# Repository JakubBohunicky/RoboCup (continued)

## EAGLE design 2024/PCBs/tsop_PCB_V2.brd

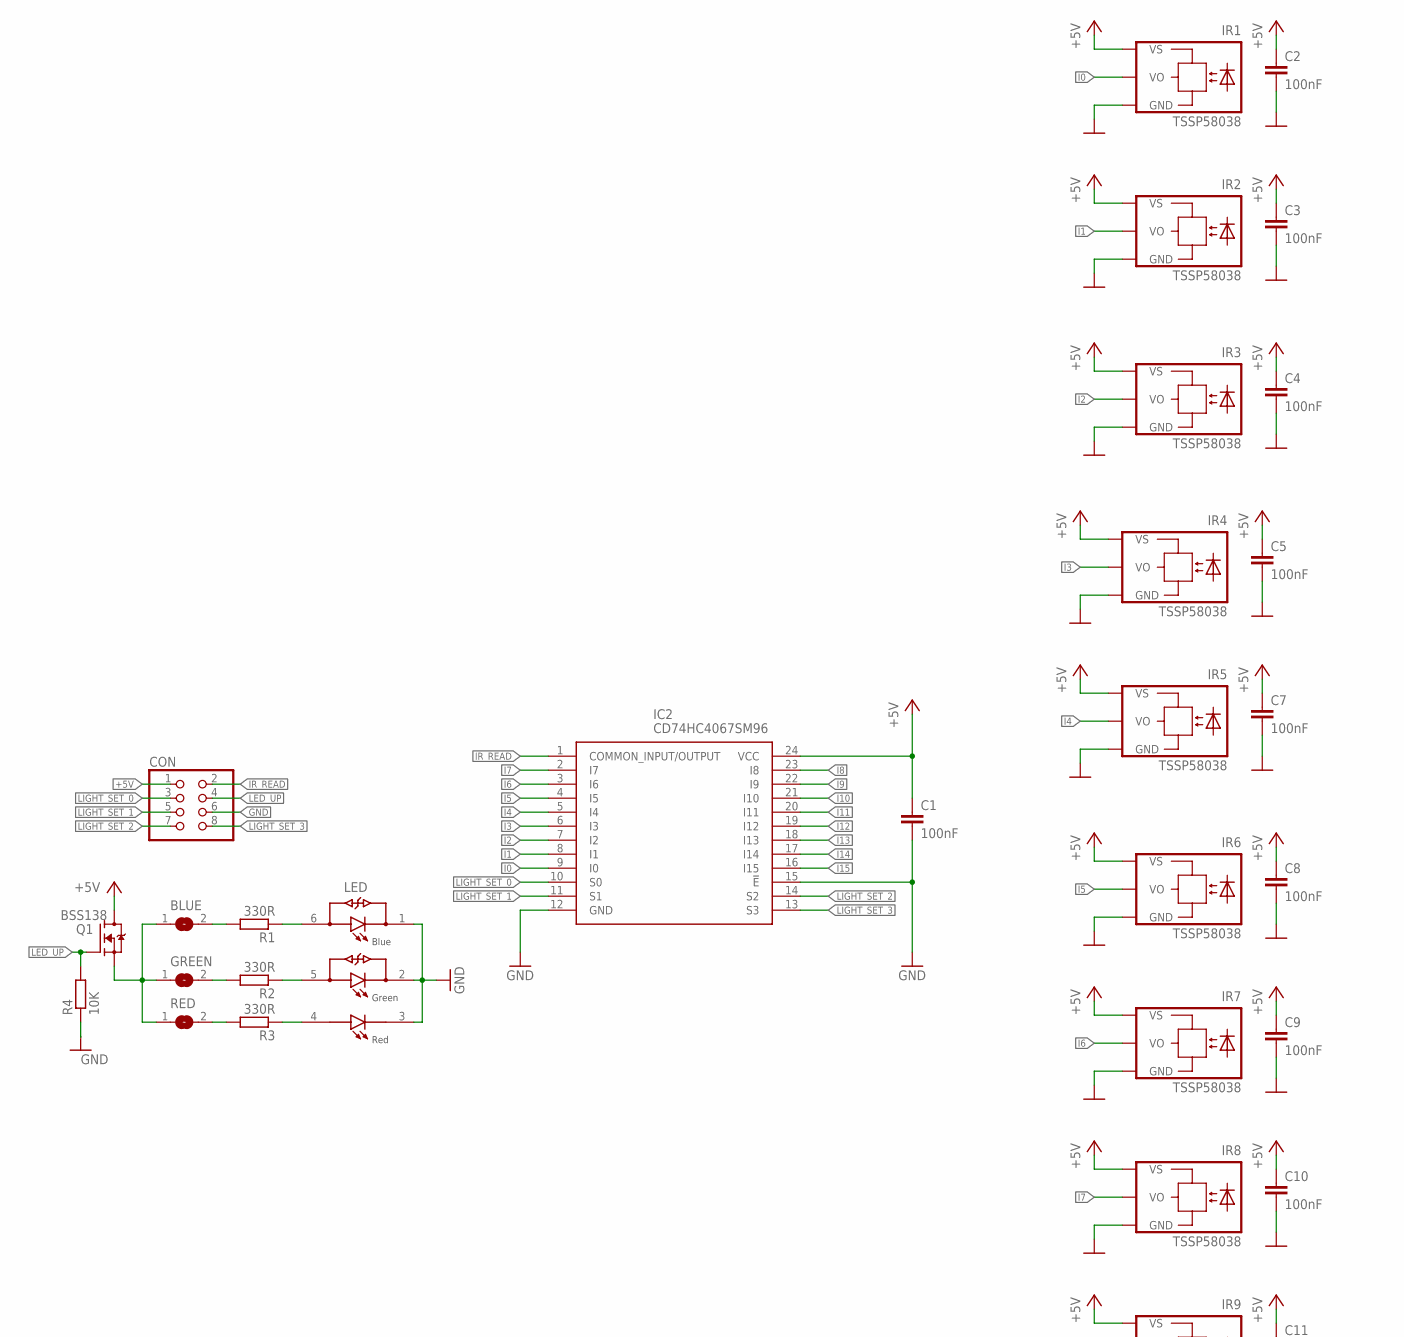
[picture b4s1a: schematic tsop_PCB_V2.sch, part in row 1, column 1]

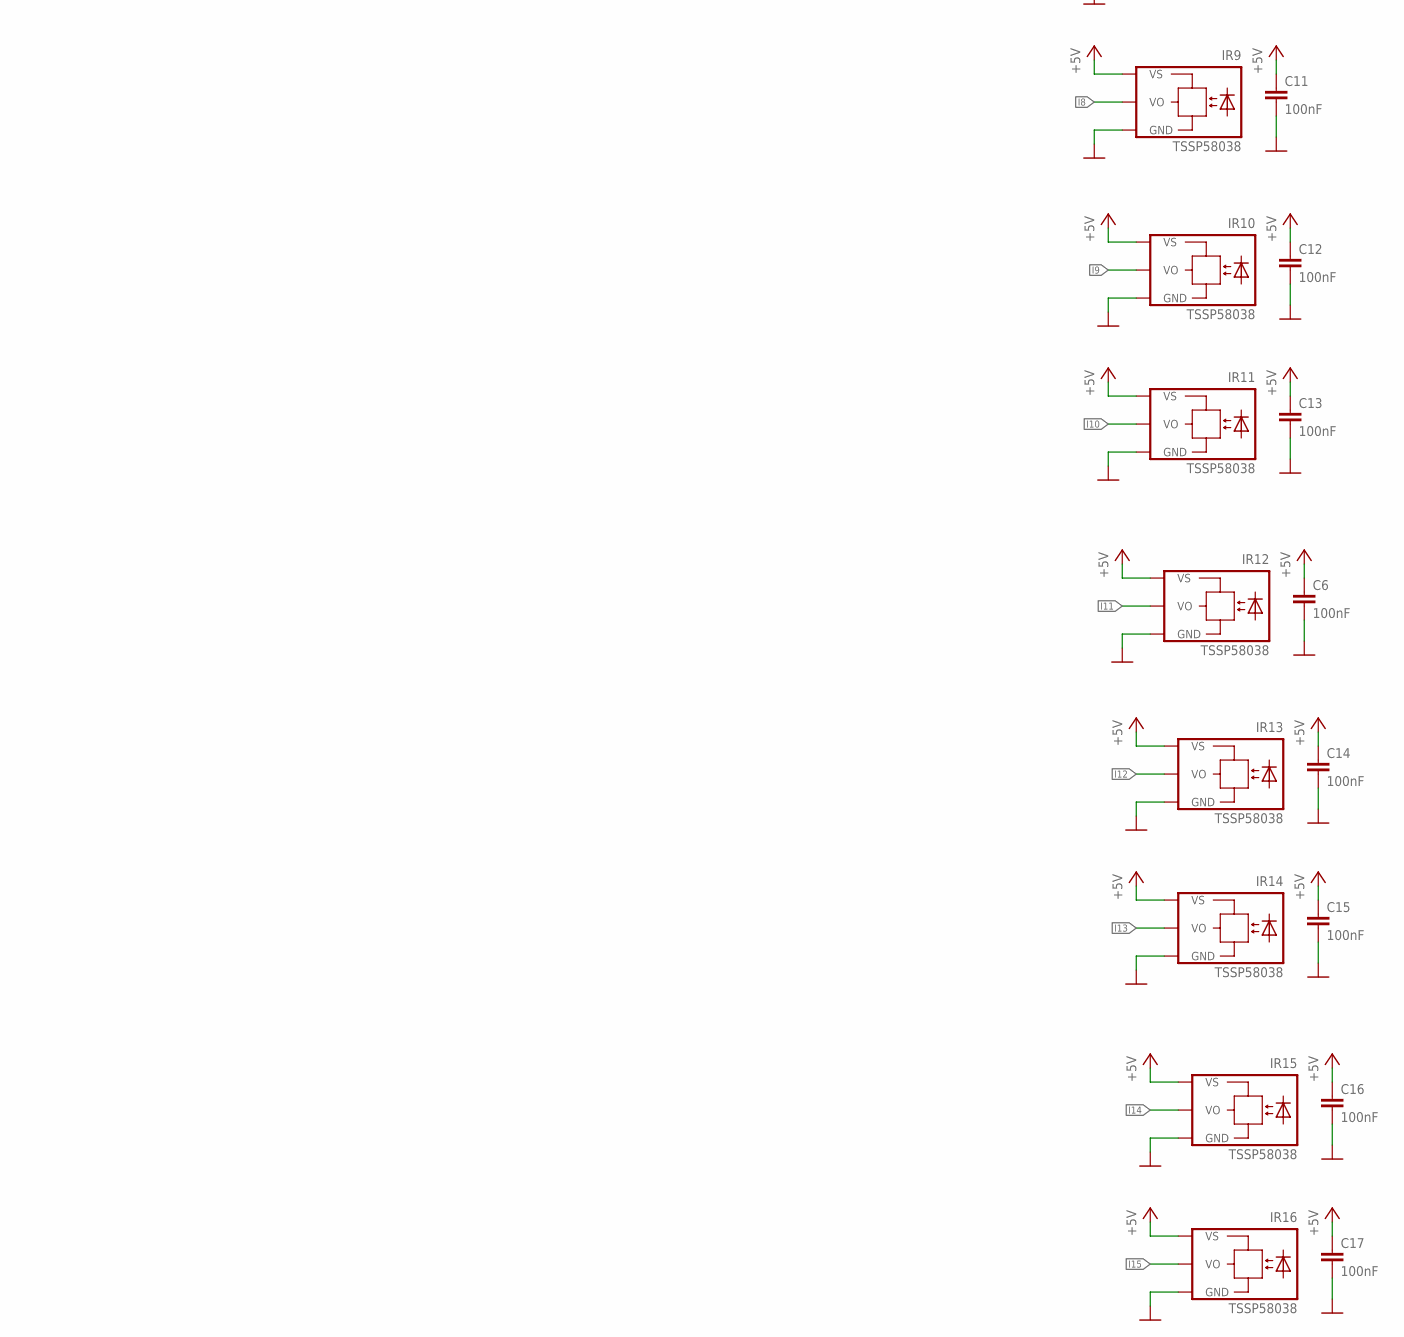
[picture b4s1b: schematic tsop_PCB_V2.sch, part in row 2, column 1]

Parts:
BLUE: SJ
C1, C2, C3, C4, C5, C6, C7, C8, C9, C10, C11, C12, C13, C14, C15, C16, C17: 100nF; C0805
CON: PINHD-2X4; 2X04
GREEN: SJ
IC2: CD74HC4067SM96; SOP65P780X200-24N
IR1, IR2, IR3, IR4, IR5, IR6, IR7, IR8, IR9, IR10, IR11, IR12, IR13, IR14, IR15, IR16: TSSP58038; TSOP
LED: LTST-G563ZEGBW; LED_LTST-G563ZEGBW
Q1: BSS138; SOT95P240X111-3N
R1, R2, R3: 330R; R1206
R4: 10K; R1206
RED: SJ

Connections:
+5V: C1.1, C2.1, C3.1, C4.1, C5.1, C6.1, C7.1, C8.1, C9.1, C10.1, C11.1, C12.1, C13.1, C14.1, C15.1, C16.1, C17.1, CON.1, IC2.24 (VCC), IR1.VS, IR2.VS, IR3.VS, IR4.VS, IR5.VS, IR6.VS, IR7.VS, IR8.VS, IR9.VS, IR10.VS, IR11.VS, IR12.VS, IR13.VS, IR14.VS, IR15.VS, IR16.VS, Q1.3 (D)
GND: C1.2, C2.2, C3.2, C4.2, C5.2, C6.2, C7.2, C8.2, C9.2, C10.2, C11.2, C12.2, C13.2, C14.2, C15.2, C16.2, C17.2, CON.6, IC2.12 (GND), IC2.15 (!E), IR1.GND, IR2.GND, IR3.GND, IR4.GND, IR5.GND, IR6.GND, IR7.GND, IR8.GND, IR9.GND, IR10.GND, IR11.GND, IR12.GND, IR13.GND, IR14.GND, IR15.GND, IR16.GND, LED.1, LED.2, LED.3, R4.1
I0: IC2.9 (I0), IR1.VO
I1: IC2.8 (I1), IR2.VO
I2: IC2.7 (I2), IR3.VO
I3: IC2.6 (I3), IR4.VO
I4: IC2.5 (I4), IR5.VO
I5: IC2.4 (I5), IR6.VO
I6: IC2.3 (I6), IR7.VO
I7: IC2.2 (I7), IR8.VO
I8: IC2.23 (I8), IR9.VO
I9: IC2.22 (I9), IR10.VO
I10: IC2.21 (I10), IR11.VO
I11: IC2.20 (I11), IR12.VO
I12: IC2.19 (I12), IR13.VO
I13: IC2.18 (I13), IR14.VO
I14: IC2.17 (I14), IR15.VO
I15: IC2.16 (I15), IR16.VO
IR_READ: CON.2, IC2.1 (COMMON_INPUT/OUTPUT)
LED_UP: CON.4, Q1.1 (G), R4.2
LIGHT_SET_0: CON.3, IC2.10 (S0)
LIGHT_SET_1: CON.5, IC2.11 (S1)
LIGHT_SET_2: CON.7, IC2.14 (S2)
LIGHT_SET_3: CON.8, IC2.13 (S3)
unnamed: LED.6, R1.1
unnamed: LED.5, R2.1
unnamed: LED.4, R3.1
unnamed: R3.2, RED.2
unnamed: GREEN.2, R2.2
unnamed: BLUE.2, R1.2
unnamed: BLUE.1, GREEN.1, Q1.2 (S), RED.1

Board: 2 copper layers, 44 parts (0 on the bottom side), 31 nets, no tracks yet.

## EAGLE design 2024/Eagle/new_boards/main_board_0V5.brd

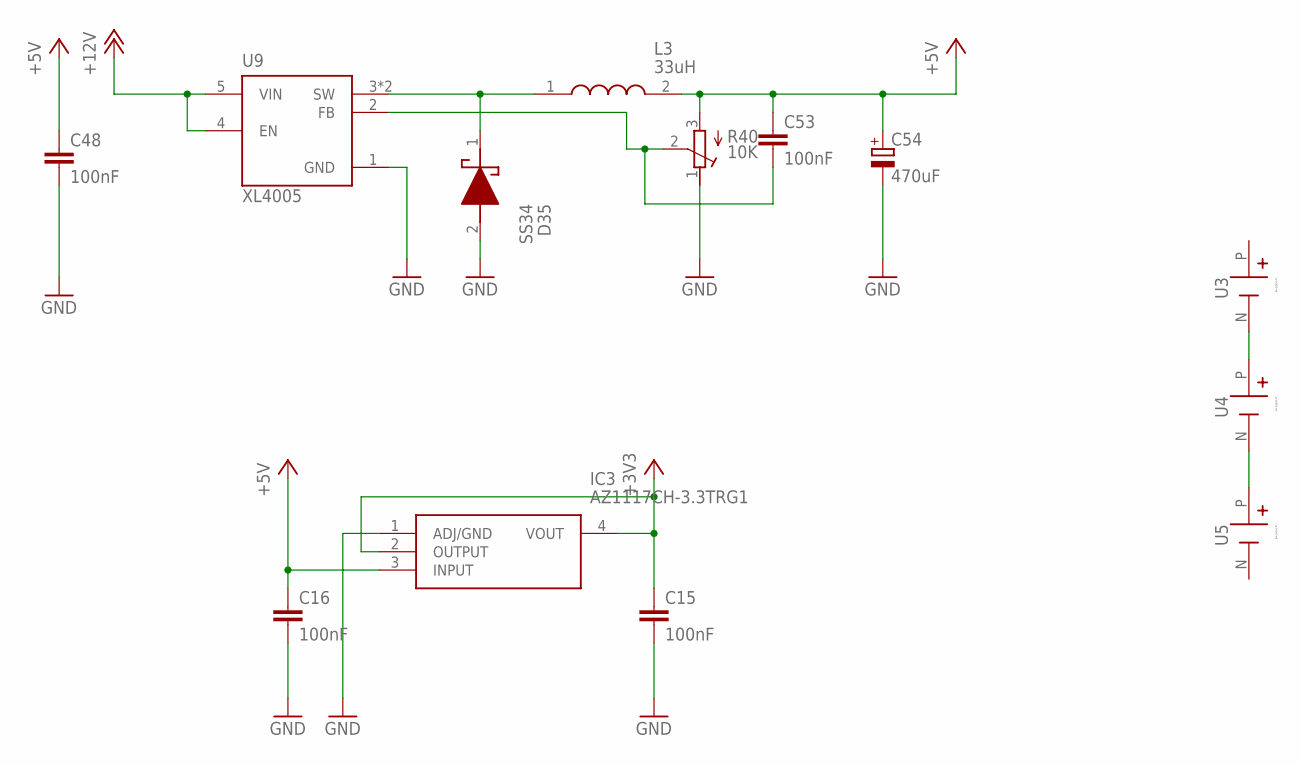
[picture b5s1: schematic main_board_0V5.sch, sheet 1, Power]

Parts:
C15, C16, C48, C53: 100nF; C0805
C54: 470uF; 150CLZ-1010
D35: SS34; DIOM8059X256N
IC3: AZ1117CH-3.3TRG1; SOT230P700X180-4N
L3: 33uH; WE-HCI_1350/136523
R40: 10K; RTRIM3314J
U3, U4, U5: BH-18650-PC; BAT_BH-18650-PC
U9: XL4005; CONV_XL4015

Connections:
+3V3: C15.1, IC3.2 (OUTPUT), IC3.4 (VOUT)
+5V: C16.1, C48.1, C53.1, C54.+, IC3.3 (INPUT), L3.2, R40.3 (A); also elsewhere on the board
+12V: U9.4 (EN), U9.5 (VIN); also elsewhere on the board
GND: C15.2, C16.2, C48.2, C54.-, D35.2 (A), IC3.1 (ADJ/GND), R40.1 (E), U9.1 (GND); also elsewhere on the board
unnamed: U4.N (-), U5.P (+)
unnamed: U3.N (-), U4.P (+)
unnamed: D35.1 (K), L3.1, U9.3 (SW), U9.3.1 (SW)
unnamed: C53.2, R40.2 (S), U9.2 (FB)

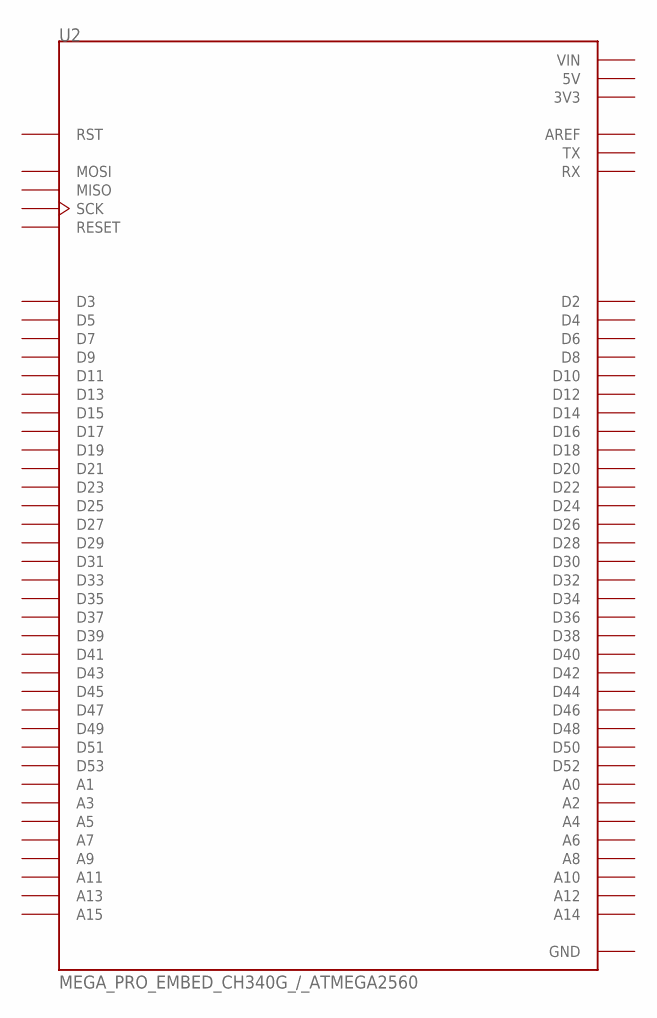
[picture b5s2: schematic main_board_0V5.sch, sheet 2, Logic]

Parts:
U2: MEGA_PRO_EMBED_CH340G_/_ATMEGA2560; MODULE_MEGA_PRO_EMBED_CH340G_/_ATMEGA2560

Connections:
3V3: U2.3V3_1 (3V3), U2.3V3_2 (3V3)
5V: U2.5V_1 (5V), U2.5V_2 (5V), U2.5V_3 (5V)
GND: U2.GND_1 (GND), U2.GND_2 (GND), U2.GND_3 (GND); also elsewhere on the board

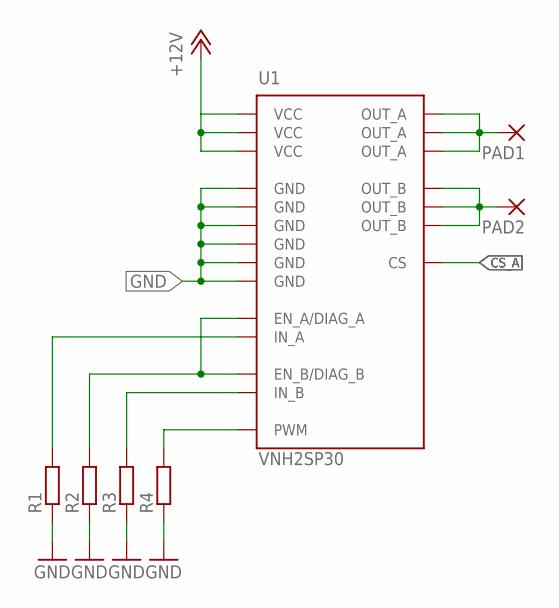
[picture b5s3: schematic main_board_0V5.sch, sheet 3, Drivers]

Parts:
PAD1, PAD2: 3,81/1,4
R1, R2, R3, R4: R-EU_R0805; R0805
U1: VNH2SP30; MULTIPOWER30

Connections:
+12V: U1.P$3 (VCC), U1.P$13 (VCC), U1.P$23 (VCC); also elsewhere on the board
CS_A: U1.P$9 (CS)
GND: R1.1, R2.1, R3.1, R4.1, U1.P$18 (GND), U1.P$19 (GND), U1.P$20 (GND), U1.P$26 (GND), U1.P$27 (GND), U1.P$28 (GND); also elsewhere on the board
unnamed: R4.2, U1.P$8 (PWM)
unnamed: R3.2, U1.P$11 (IN_B)
unnamed: R1.2, U1.P$5 (IN_A)
unnamed: R2.2, U1.P$6 (EN_A/DIAG_A), U1.P$10 (EN_B/DIAG_B)
unnamed: PAD2.1, U1.P$15 (OUT_B), U1.P$16 (OUT_B), U1.P$21 (OUT_B)
unnamed: PAD1.1, U1.P$1 (OUT_A), U1.P$25 (OUT_A), U1.P$30 (OUT_A)

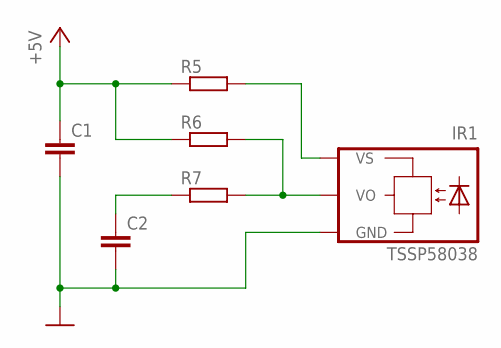
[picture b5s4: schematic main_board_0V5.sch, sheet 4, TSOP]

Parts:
C1, C2: C-EUC0805; C0805
IR1: TSSP58038; TSOP
R5, R6, R7: R-EU_R0805; R0805

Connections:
+5V: C1.1, R5.1, R6.1; also elsewhere on the board
GND: C1.2, C2.2, IR1.GND; also elsewhere on the board
unnamed: IR1.VS, R5.2
unnamed: C2.1, R7.1
unnamed: IR1.VO, R6.2, R7.2

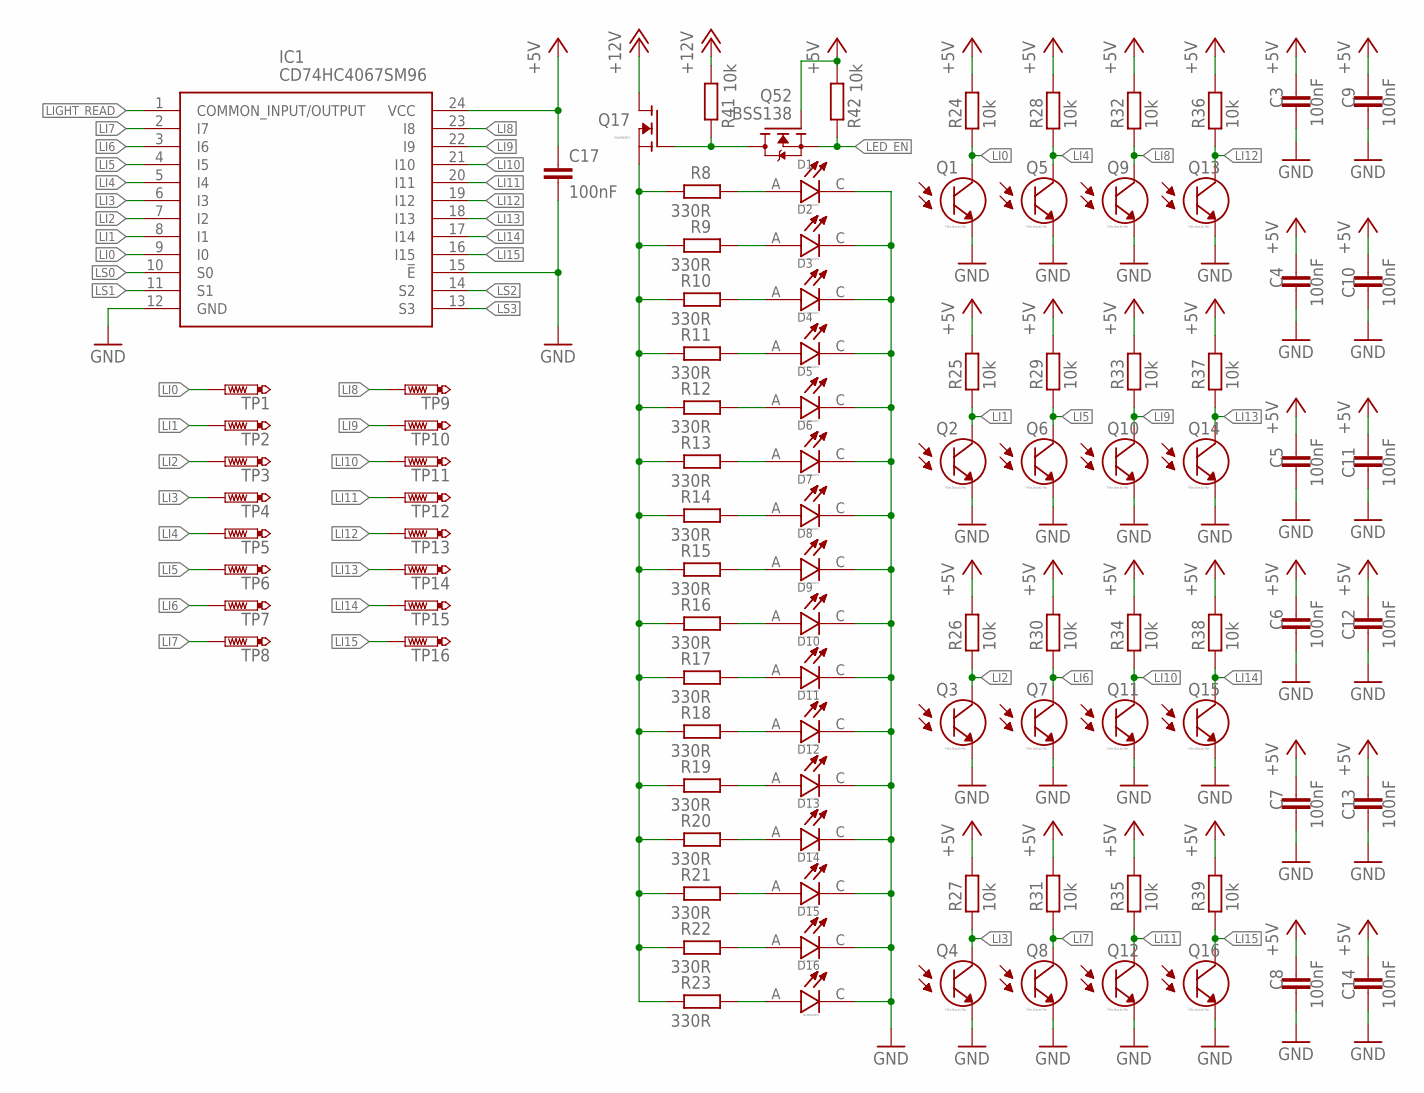
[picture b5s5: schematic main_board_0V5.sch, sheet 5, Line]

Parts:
C3, C4, C5, C6, C7, C8, C9, C10, C11, C12, C13, C14, C17: 100nF; C0805
D1, D2, D3, D4, D5, D6, D7, D8, D9, D10, D11, D12, D13, D14, D15, D16: OF-SMD2835Y; LED_OF-SMD2835Y
IC1: CD74HC4067SM96; SOP65P780X200-24N
Q1, Q2, Q3, Q4, Q5, Q6, Q7, Q8, Q9, Q10, Q11, Q12, Q13, Q14, Q15, Q16: PT19-21B/L41/TR8; XDCR_PT19-21B/L41/TR8
Q17: CSD19503KCS; TO254P1036X470X1965-3
Q52: BSS138; SOT95P240X111-3N
R8, R9, R10, R11, R12, R13, R14, R15, R16, R17, R18, R19, R20, R21, R22, R23: 330R; R0805
R24, R25, R26, R27, R28, R29, R30, R31, R32, R33, R34, R35, R36, R37, R38, R39: 10k; R0805
R41, R42: 10k; R1206
TP1, TP2, TP3, TP4, TP5, TP6, TP7, TP8, TP9, TP10, TP11, TP12, TP13, TP14, TP15, TP16: PTR1PAD1-13; P1-13

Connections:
+5V: C3.2, C4.2, C5.2, C6.2, C7.2, C8.2, C9.2, C10.2, C11.2, C12.2, C13.2, C14.2, C17.1, IC1.24 (VCC), Q52.1 (G), R24.1, R25.1, R26.1, R27.1, R28.1, R29.1, R30.1, R31.1, R32.1, R33.1, R34.1, R35.1, R36.1, R37.1, R38.1, R39.1, R42.2; also elsewhere on the board
+5V_UP: R41.2
+12V: Q17.2 (D); also elsewhere on the board
GND: C3.1, C4.1, C5.1, C6.1, C7.1, C8.1, C9.1, C10.1, C11.1, C12.1, C13.1, C14.1, C17.2, IC1.12 (GND), IC1.15 (!E), Q1.E, Q2.E, Q3.E, Q4.E, Q5.E, Q6.E, Q7.E, Q8.E, Q9.E, Q10.E, Q11.E, Q12.E, Q13.E, Q14.E, Q15.E, Q16.E; also elsewhere on the board
LED_EN: Q52.2 (S), R42.1
LI0: IC1.9 (I0), Q1.C, R24.2, TP1.TP
LI1: IC1.8 (I1), Q2.C, R25.2, TP2.TP
LI2: IC1.7 (I2), Q3.C, R26.2, TP3.TP
LI3: IC1.6 (I3), Q4.C, R27.2, TP4.TP
LI4: IC1.5 (I4), Q5.C, R28.2, TP5.TP
LI5: IC1.4 (I5), Q6.C, R29.2, TP6.TP
LI6: IC1.3 (I6), Q7.C, R30.2, TP7.TP
LI7: IC1.2 (I7), Q8.C, R31.2, TP8.TP
LI8: IC1.23 (I8), Q9.C, R32.2, TP9.TP
LI9: IC1.22 (I9), Q10.C, R33.2, TP10.TP
LI10: IC1.21 (I10), Q11.C, R34.2, TP11.TP
LI11: IC1.20 (I11), Q12.C, R35.2, TP12.TP
LI12: IC1.19 (I12), Q13.C, R36.2, TP13.TP
LI13: IC1.18 (I13), Q14.C, R37.2, TP14.TP
LI14: IC1.17 (I14), Q15.C, R38.2, TP15.TP
LI15: IC1.16 (I15), Q16.C, R39.2, TP16.TP
LIGHT_READ: IC1.1 (COMMON_INPUT/OUTPUT)
LS0: IC1.10 (S0)
LS1: IC1.11 (S1)
LS2: IC1.14 (S2)
LS3: IC1.13 (S3)
unnamed: D1.A, R8.1
unnamed: D9.A, R16.1
unnamed: D10.A, R17.1
unnamed: D2.A, R9.1
unnamed: D11.A, R18.1
unnamed: D3.A, R10.1
unnamed: D12.A, R19.1
unnamed: D4.A, R11.1
unnamed: D13.A, R20.1
unnamed: D5.A, R12.1
unnamed: D14.A, R21.1
unnamed: D6.A, R13.1
unnamed: D15.A, R22.1
unnamed: D7.A, R14.1
unnamed: D16.A, R23.1
unnamed: D8.A, R15.1
unnamed: D1.C, D2.C, D3.C, D4.C, D5.C, D6.C, D7.C, D8.C, D9.C, D10.C, D11.C, D12.C, D13.C, D14.C, D15.C, D16.C
unnamed: Q17.3 (S), R8.2, R9.2, R10.2, R11.2, R12.2, R13.2, R14.2, R15.2, R16.2, R17.2, R18.2, R19.2, R20.2, R21.2, R22.2, R23.2
unnamed: Q17.1 (G), Q52.3 (D), R41.1

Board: 2 copper layers, 125 parts (0 on the bottom side), 55 nets, no tracks yet.

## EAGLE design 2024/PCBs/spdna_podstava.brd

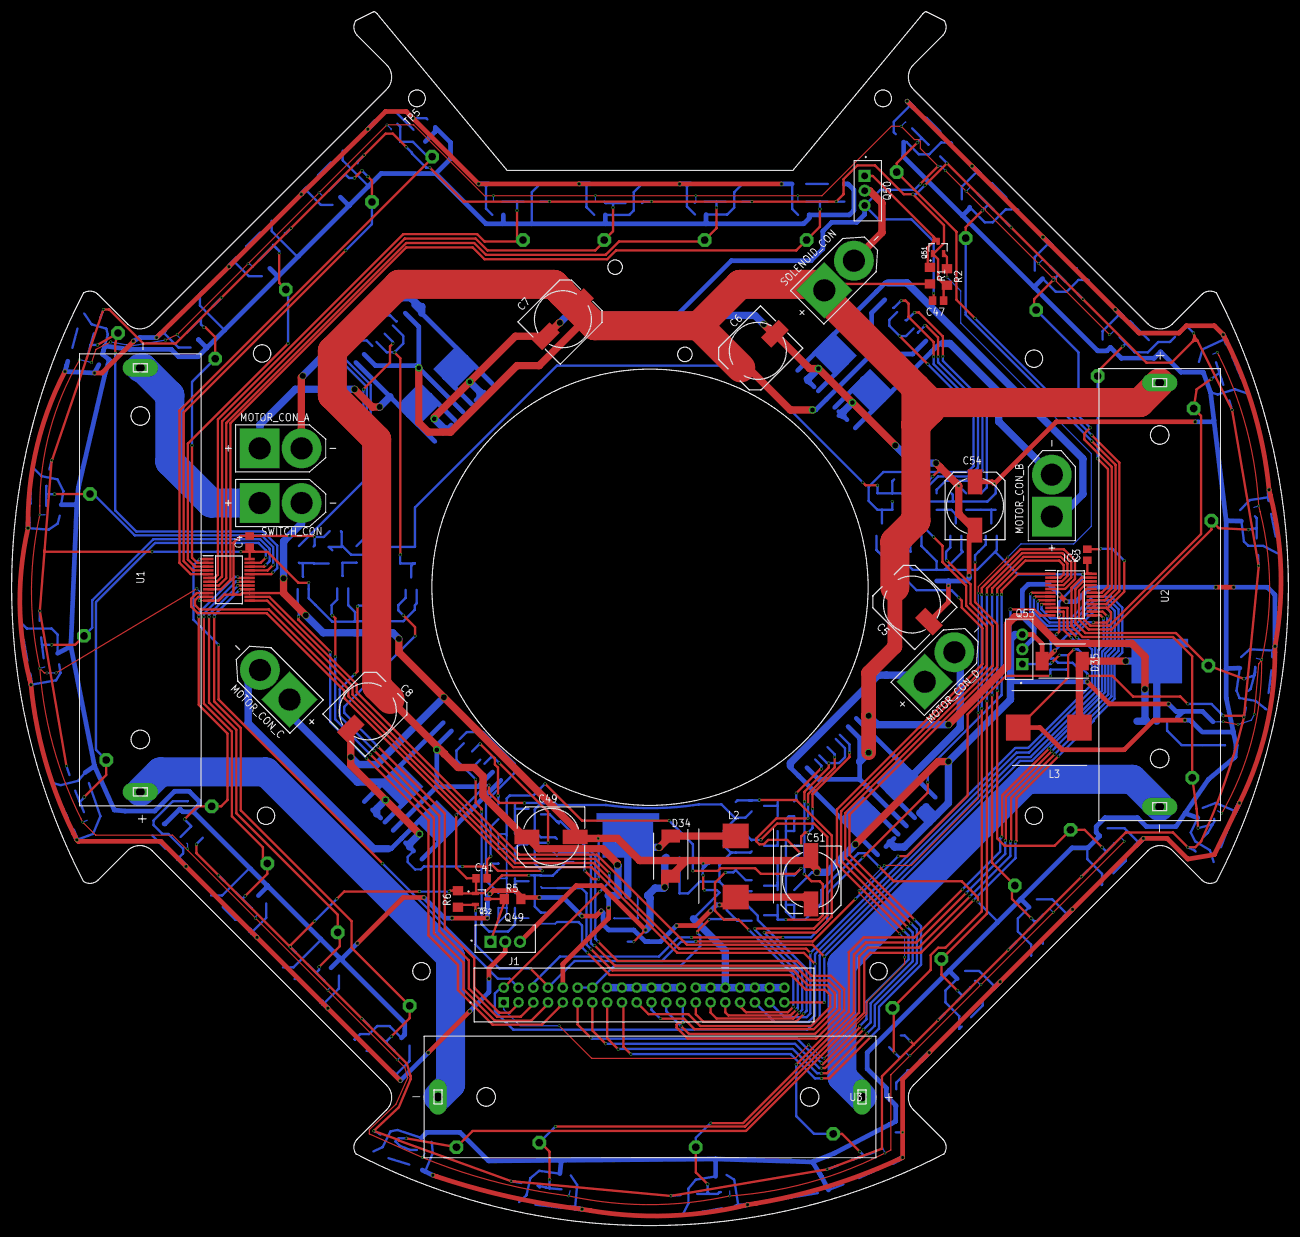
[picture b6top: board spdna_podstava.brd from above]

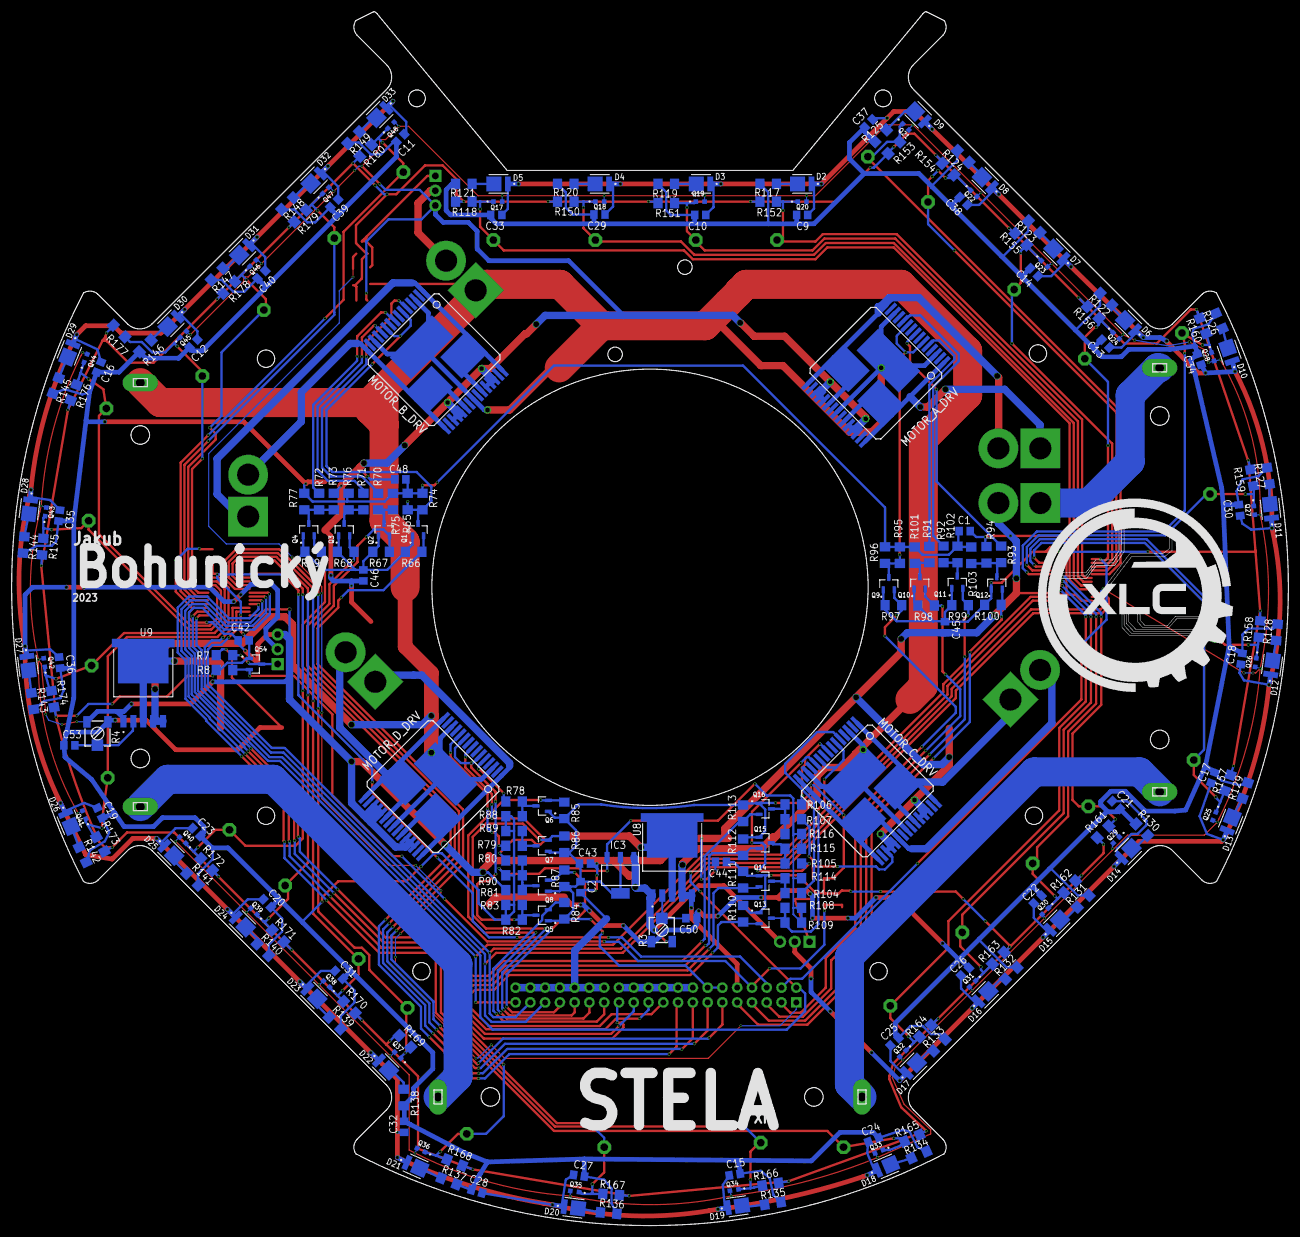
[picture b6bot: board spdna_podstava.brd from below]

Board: 2 copper layers, 219.5 x 208.7 mm, 318 parts (250 on the bottom side), 143 nets.

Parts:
C1, C2, C3, C4, C9, C10, C11, C12, C13, C14, C15, C16, C17, C18, C19, C20, C21, C22, C23, C24, C25, C26, C27, C28, C29, C30, C31, C32, C33, C34, C35, C36, C37, C38, C39, C40, C41, C42, C43, C44, C45, C46, C47, C48, C50, C53: 100nF; C0805
C5, C6, C7, C8, C49, C51, C54: 470uF; 150CLZ-1010
D2, D3, D4, D5, D6, D7, D8, D9, D10, D11, D12, D13, D14, D15, D16, D17, D18, D19, D20, D21, D22, D23, D24, D25, D26, D27, D28, D29, D30, D31, D32, D33: OF-SMD2835Y; LED_OF-SMD2835Y
D34, D35: SS34; DIOM8059X256N
IC1, IC2: CD74HC4067SM96; SOP65P780X200-24N
IC3: AZ1117CH-3.3TRG1; SOT230P700X180-4N
J1: TST-120-02-S-D; SAMTEC_TST-120-02-S-D
L2, L3: 33uH; WE-HCI_1350/136523
MOTOR_A_DRV: VNH2SP30; MULTIPOWER30
MOTOR_B_DRV: VNH2SP30; MULTIPOWER30
MOTOR_CON_A: XT60-M; AMASS_XT60-M
MOTOR_CON_B: XT60-M; AMASS_XT60-M
MOTOR_CON_C: XT60-M; AMASS_XT60-M
MOTOR_CON_D: XT60-M; AMASS_XT60-M
MOTOR_C_DRV: VNH2SP30; MULTIPOWER30
MOTOR_D_DRV: VNH2SP30; MULTIPOWER30
Q1, Q2, Q3, Q4, Q5, Q6, Q7, Q8, Q9, Q10, Q11, Q12, Q13, Q14, Q15, Q16, Q51, Q52, Q54: BSS138; SOT95P240X111-3N
Q17, Q18, Q19, Q20, Q21, Q22, Q23, Q24, Q25, Q26, Q27, Q28, Q29, Q30, Q31, Q32, Q33, Q34, Q35, Q36, Q37, Q38, Q39, Q40, Q41, Q42, Q43, Q44, Q45, Q46, Q47, Q48: PT19-21B/L41/TR8; XDCR_PT19-21B/L41/TR8
Q49, Q50, Q53: CSD19503KCS; TO254P1036X470X1965-3
R1, R2, R5, R6, R7, R8, R65, R66, R67, R68, R69, R73, R75, R76, R77, R81, R83, R84, R85, R86, R87, R88, R89, R90, R94, R96, R97, R98, R99, R100, R101, R102, R103, R107, R109, R110, R111, R112, R113, R114, R115, R116, R118, R150, R151, R152, R153, R154, R155, R156, R157, R158, R159, R160, R161, R162, R163, R164, R165, R166, R167, R168, R169, R170, R171, R172, R173, R174, R175, R176, R177, R178, R179, R180: 10k; R1206
R3, R4: 10K; RTRIM3314J
R70, R71, R72, R78, R79, R80, R91, R92, R93, R104, R105, R106: 1k; R1206
R74, R82, R95, R108: 4.7k; R1206
R117, R119, R120, R121, R122, R123, R124, R125, R126, R127, R128, R129, R130, R131, R132, R133, R134, R135, R136, R137, R138, R139, R140, R141, R142, R143, R144, R145, R146, R147, R148, R149: 10R; R1206
SOLENOID_CON: XT60-M; AMASS_XT60-M
SWITCH_CON: XT60-M; AMASS_XT60-M
TP1, TP2, TP3, TP4, TP5, TP6, TP7, TP8, TP9, TP10, TP11, TP12, TP13, TP14, TP15, TP16, TP17, TP18, TP19, TP20, TP21, TP22, TP23, TP24, TP25, TP26, TP27, TP28, TP29, TP30, TP31, TP32: PTR1PAD1-13; P1-13
U1, U2, U3: BH-18650-PC; BAT_BH-18650-PC
U8, U9: XL4005; CONV_XL4015

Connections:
+3V3: C2.1, C3.1, C4.1, C41.1, C42.1, C43.1, C44.1, C45.1, C46.1, C47.1, IC1.24, IC2.24, IC3.2, IC3.4, J1.12, J1.14, Q1.1, Q2.1, Q3.1, Q4.1, Q5.1, Q6.1, Q7.1, Q8.1, Q9.1, Q10.1, Q11.1, Q12.1, Q13.1, Q14.1, Q15.1, Q16.1, Q51.1, Q52.1, Q54.1, R2.2, R6.2, R8.2, R66.2, R67.2, R68.2, R69.2, R84.2, R85.2, R86.2, R87.2, R97.2, R98.2, R99.2, R100.2, R110.2, R111.2, R112.2, R113.2, R118.1, R150.1, R151.1, R152.1, R153.1, R154.1, R155.1, R156.1, R157.1, R158.1, R159.1, R160.1, R161.1, R162.1, R163.1, R164.1, R165.1, R166.1, R167.1, R168.1, R169.1, R170.1, R171.1, R172.1, R173.1, R174.1, R175.1, R176.1, R177.1, R178.1, R179.1, R180.1
+5V: C1.1, C11.2, C12.2, C15.2, C16.2, C19.2, C20.2, C23.2, C24.2, C27.2, C28.2, C31.2, C32.2, C35.2, C36.2, C39.2, C40.2, C48.1, C53.1, C54.+, IC3.3, L3.2, R4.3, R7.2, R65.2, R74.2, R75.2, R76.2, R77.2, R82.2, R83.2, R88.2, R89.2, R90.2, R95.2, R96.2, R101.2, R102.2, R103.2, R108.2, R109.2, R114.2, R115.2, R116.2, R134.2, R135.2, R136.2, R137.2, R138.2, R139.2, R140.2, R141.2, R142.2, R143.2, R144.2, R145.2, R146.2, R147.2, R148.2, R149.2
+5V_UP: C9.2, C10.2, C13.2, C14.2, C17.2, C18.2, C21.2, C22.2, C25.2, C26.2, C29.2, C30.2, C33.2, C34.2, C37.2, C38.2, C50.1, C51.+, L2.2, R3.3, R5.2, R117.2, R119.2, R120.2, R121.2, R122.2, R123.2, R124.2, R125.2, R126.2, R127.2, R128.2, R129.2, R130.2, R131.2, R132.2, R133.2
+5_UP: J1.16, J1.18, J1.20, J1.22, J1.24, J1.26
+12V: C5.+, C6.+, C7.+, C8.+, C49.+, J1.10, MOTOR_A_DRV.P$3, MOTOR_A_DRV.P$13, MOTOR_A_DRV.P$23, MOTOR_B_DRV.P$3, MOTOR_B_DRV.P$13, MOTOR_B_DRV.P$23, MOTOR_C_DRV.P$3, MOTOR_C_DRV.P$13, MOTOR_C_DRV.P$23, MOTOR_D_DRV.P$3, MOTOR_D_DRV.P$13, MOTOR_D_DRV.P$23, R1.2, SOLENOID_CON.P, U2.P, U8.4, U8.5, U9.4, U9.5
EN_A: J1.03, Q9.2, R97.1
EN_B: J1.11, Q1.2, R66.1
EN_C: J1.19, Q13.2, R110.1
EN_D: J1.27, Q5.2, R84.1
GND: C1.2, C2.2, C3.2, C4.2, C5.-, C6.-, C7.-, C8.-, C41.2, C42.2, C43.2, C44.2, C45.2, C46.2, C47.2, C48.2, C49.-, C51.-, C54.-, D34.2, D35.2, IC1.12, IC1.15, IC2.12, IC2.15, IC3.1, J1.28, J1.30, J1.32, J1.34, J1.36, J1.38, J1.40, MOTOR_A_DRV.P$18, MOTOR_A_DRV.P$19, MOTOR_A_DRV.P$20, MOTOR_A_DRV.P$26, MOTOR_A_DRV.P$27, MOTOR_A_DRV.P$28, MOTOR_B_DRV.P$18, MOTOR_B_DRV.P$19, MOTOR_B_DRV.P$20, MOTOR_B_DRV.P$26, MOTOR_B_DRV.P$27, MOTOR_B_DRV.P$28, MOTOR_C_DRV.P$18, MOTOR_C_DRV.P$19, MOTOR_C_DRV.P$20, MOTOR_C_DRV.P$26, MOTOR_C_DRV.P$27, MOTOR_C_DRV.P$28, MOTOR_D_DRV.P$18, MOTOR_D_DRV.P$19, MOTOR_D_DRV.P$20, MOTOR_D_DRV.P$26, MOTOR_D_DRV.P$27, MOTOR_D_DRV.P$28, Q17.E, Q18.E, Q19.E, Q20.E, Q21.E, Q22.E, Q23.E, Q24.E, Q25.E, Q26.E, Q27.E, Q28.E, Q29.E, Q30.E, Q31.E, Q32.E, Q33.E, Q34.E, Q35.E, Q36.E, Q37.E, Q38.E, Q39.E, Q40.E, Q41.E, Q42.E, Q43.E, Q44.E, Q45.E, Q46.E, Q47.E, Q48.E, Q49.3, Q50.3, Q53.3, R3.1, R4.1, R73.2, R81.2, R94.2, R107.2, SWITCH_CON.N, U8.1, U9.1
IN1_A: J1.05, Q10.2, R98.1
IN1_B: J1.13, Q2.2, R67.1
IN1_C: J1.21, Q14.2, R111.1
IN1_D: J1.29, Q6.2, R85.1
IN2_A: J1.07, Q11.2, R99.1
IN2_B: J1.15, Q3.2, R68.1
IN2_C: J1.23, Q15.2, R112.1
IN2_D: J1.31, Q7.2, R86.1
KICKER: J1.01, Q51.2, R2.1
LED_ENABLE: J1.08, Q52.2, Q54.2, R6.1, R8.1
LIGHT_I0: IC1.9, Q17.C, R118.2, TP1.TP
LIGHT_I1: IC1.8, Q18.C, R150.2, TP2.TP
LIGHT_I2: IC1.7, Q19.C, R151.2, TP3.TP
LIGHT_I3: IC1.6, Q20.C, R152.2, TP4.TP
LIGHT_I4: IC1.5, Q21.C, R153.2, TP5.TP
LIGHT_I5: IC1.4, Q22.C, R154.2, TP6.TP
LIGHT_I6: IC1.3, Q23.C, R155.2, TP7.TP
LIGHT_I7: IC1.2, Q24.C, R156.2, TP8.TP
LIGHT_I8: IC1.23, Q25.C, R157.2, TP9.TP
LIGHT_I9: IC1.22, Q26.C, R158.2, TP10.TP
LIGHT_I10: IC1.21, Q27.C, R159.2, TP11.TP
LIGHT_I11: IC1.20, Q28.C, R160.2, TP12.TP
LIGHT_I12: IC1.19, Q29.C, R161.2, TP13.TP
LIGHT_I13: IC1.18, Q30.C, R162.2, TP14.TP
LIGHT_I14: IC1.17, Q31.C, R163.2, TP15.TP
LIGHT_I15: IC1.16, Q32.C, R164.2, TP16.TP
LIGHT_I16: IC2.9, Q33.C, R165.2, TP17.TP
LIGHT_I17: IC2.8, Q34.C, R166.2, TP18.TP
LIGHT_I18: IC2.7, Q35.C, R167.2, TP19.TP
LIGHT_I19: IC2.6, Q36.C, R168.2, TP20.TP
LIGHT_I20: IC2.5, Q37.C, R169.2, TP21.TP
LIGHT_I21: IC2.4, Q38.C, R170.2, TP22.TP
LIGHT_I22: IC2.3, Q39.C, R171.2, TP23.TP
LIGHT_I23: IC2.2, Q40.C, R172.2, TP24.TP
LIGHT_I24: IC2.23, Q41.C, R173.2, TP25.TP
LIGHT_I25: IC2.22, Q42.C, R174.2, TP26.TP
LIGHT_I26: IC2.21, Q43.C, R175.2, TP27.TP
LIGHT_I27: IC2.20, Q44.C, R176.2, TP28.TP
LIGHT_I28: IC2.19, Q45.C, R177.2, TP29.TP
LIGHT_I29: IC2.18, Q46.C, R178.2, TP30.TP
LIGHT_I30: IC2.17, Q47.C, R179.2, TP31.TP
LIGHT_I31: IC2.16, Q48.C, R180.2, TP32.TP
LIGHT_READ_A: IC1.1, J1.04
LIGHT_READ_B: IC2.1, J1.06
LIGHT_SET_0: IC1.10, IC2.10, J1.35
LIGHT_SET_1: IC1.11, IC2.11, J1.37
LIGHT_SET_2: IC1.14, IC2.14, J1.39
LIGHT_SET_3: IC1.13, IC2.13, J1.02
unnamed: Q50.2, SOLENOID_CON.N
unnamed: Q50.1, Q51.3, R1.1
unnamed: D34.1, L2.1, U8.3, U8.3.1
unnamed: D35.1, L3.1, U9.3, U9.3.1
unnamed: C50.2, R3.2, U8.2
unnamed: C53.2, R4.2, U9.2
unnamed: U2.N, U3.P
unnamed: U1.P, U3.N
unnamed: SWITCH_CON.P, U1.N
unnamed: Q49.1, Q52.3, R5.1
unnamed: Q53.1, Q54.3, R7.1
unnamed: C9.1, C10.1, C13.1, C14.1, C17.1, C18.1, C21.1, C22.1, C25.1, C26.1, C29.1, C30.1, C33.1, C34.1, C37.1, C38.1, D2.C, D3.C, D4.C, D5.C, D6.C, D7.C, D8.C, D9.C, D10.C, D11.C, D12.C, D13.C, D14.C, D15.C, D16.C, D17.C, Q49.2
unnamed: C11.1, C12.1, C15.1, C16.1, C19.1, C20.1, C23.1, C24.1, C27.1, C28.1, C31.1, C32.1, C35.1, C36.1, C39.1, C40.1, D18.C, D19.C, D20.C, D21.C, D22.C, D23.C, D24.C, D25.C, D26.C, D27.C, D28.C, D29.C, D30.C, D31.C, D32.C, D33.C, Q53.2
unnamed: MOTOR_CON_D.P, MOTOR_D_DRV.P$1, MOTOR_D_DRV.P$25, MOTOR_D_DRV.P$30
unnamed: MOTOR_CON_D.N, MOTOR_D_DRV.P$15, MOTOR_D_DRV.P$16, MOTOR_D_DRV.P$21
unnamed: MOTOR_D_DRV.P$8, R80.1
unnamed: MOTOR_B_DRV.P$1, MOTOR_B_DRV.P$25, MOTOR_B_DRV.P$30, MOTOR_CON_B.P
unnamed: MOTOR_D_DRV.P$11, R79.2
unnamed: MOTOR_D_DRV.P$5, R78.2
unnamed: MOTOR_B_DRV.P$15, MOTOR_B_DRV.P$16, MOTOR_B_DRV.P$21, MOTOR_CON_B.N
unnamed: MOTOR_B_DRV.P$8, R72.1
unnamed: MOTOR_B_DRV.P$11, R71.2
unnamed: MOTOR_B_DRV.P$5, R70.2
unnamed: Q6.3, R78.1, R88.1
unnamed: Q7.3, R79.1, R89.1
unnamed: Q8.3, R80.2, R81.1, R90.1
unnamed: MOTOR_D_DRV.P$6, MOTOR_D_DRV.P$10, Q5.3, R82.1, R83.1
unnamed: MOTOR_A_DRV.P$1, MOTOR_A_DRV.P$25, MOTOR_A_DRV.P$30, MOTOR_CON_A.P
unnamed: MOTOR_A_DRV.P$15, MOTOR_A_DRV.P$16, MOTOR_A_DRV.P$21, MOTOR_CON_A.N
unnamed: MOTOR_A_DRV.P$8, R93.1
unnamed: MOTOR_A_DRV.P$11, R92.2
unnamed: MOTOR_A_DRV.P$5, R91.2
unnamed: Q10.3, R91.1, R101.1
unnamed: Q11.3, R92.1, R102.1
unnamed: Q12.3, R93.2, R94.1, R103.1
unnamed: MOTOR_A_DRV.P$6, MOTOR_A_DRV.P$10, Q9.3, R95.1, R96.1
unnamed: MOTOR_CON_C.P, MOTOR_C_DRV.P$1, MOTOR_C_DRV.P$25, MOTOR_C_DRV.P$30
unnamed: MOTOR_CON_C.N, MOTOR_C_DRV.P$15, MOTOR_C_DRV.P$16, MOTOR_C_DRV.P$21
unnamed: MOTOR_C_DRV.P$8, R106.1
unnamed: MOTOR_C_DRV.P$11, R105.2
unnamed: MOTOR_C_DRV.P$5, R104.2
unnamed: Q14.3, R104.1, R114.1
unnamed: Q15.3, R105.1, R115.1
unnamed: Q16.3, R106.2, R107.1, R116.1
unnamed: MOTOR_C_DRV.P$6, MOTOR_C_DRV.P$10, Q13.3, R108.1, R109.1
unnamed: D2.A, R117.1
unnamed: D3.A, R119.1
unnamed: D4.A, R120.1
unnamed: D5.A, R121.1
unnamed: D6.A, R122.1
unnamed: D7.A, R123.1
unnamed: D8.A, R124.1
unnamed: D9.A, R125.1
unnamed: D10.A, R126.1
unnamed: D11.A, R127.1
unnamed: D12.A, R128.1
unnamed: D13.A, R129.1
unnamed: Q4.3, R72.2, R73.1, R77.1
unnamed: Q3.3, R71.1, R76.1
unnamed: Q2.3, R70.1, R75.1
unnamed: MOTOR_B_DRV.P$6, MOTOR_B_DRV.P$10, Q1.3, R65.1, R74.1
unnamed: D14.A, R130.1
unnamed: D15.A, R131.1
unnamed: D16.A, R132.1
unnamed: D17.A, R133.1
unnamed: D18.A, R134.1
unnamed: D19.A, R135.1
unnamed: D20.A, R136.1
unnamed: D21.A, R137.1
unnamed: D22.A, R138.1
unnamed: D23.A, R139.1
unnamed: D24.A, R140.1
unnamed: D25.A, R141.1
unnamed: D26.A, R142.1
unnamed: D27.A, R143.1
unnamed: D28.A, R144.1
unnamed: D29.A, R145.1
unnamed: D30.A, R146.1
unnamed: D31.A, R147.1
unnamed: D32.A, R148.1
unnamed: D33.A, R149.1
PWM_A: J1.09, Q12.2, R100.1
PWM_B: J1.17, Q4.2, R69.1
PWM_C: J1.25, Q16.2, R113.1
PWM_D: J1.33, Q8.2, R87.1
